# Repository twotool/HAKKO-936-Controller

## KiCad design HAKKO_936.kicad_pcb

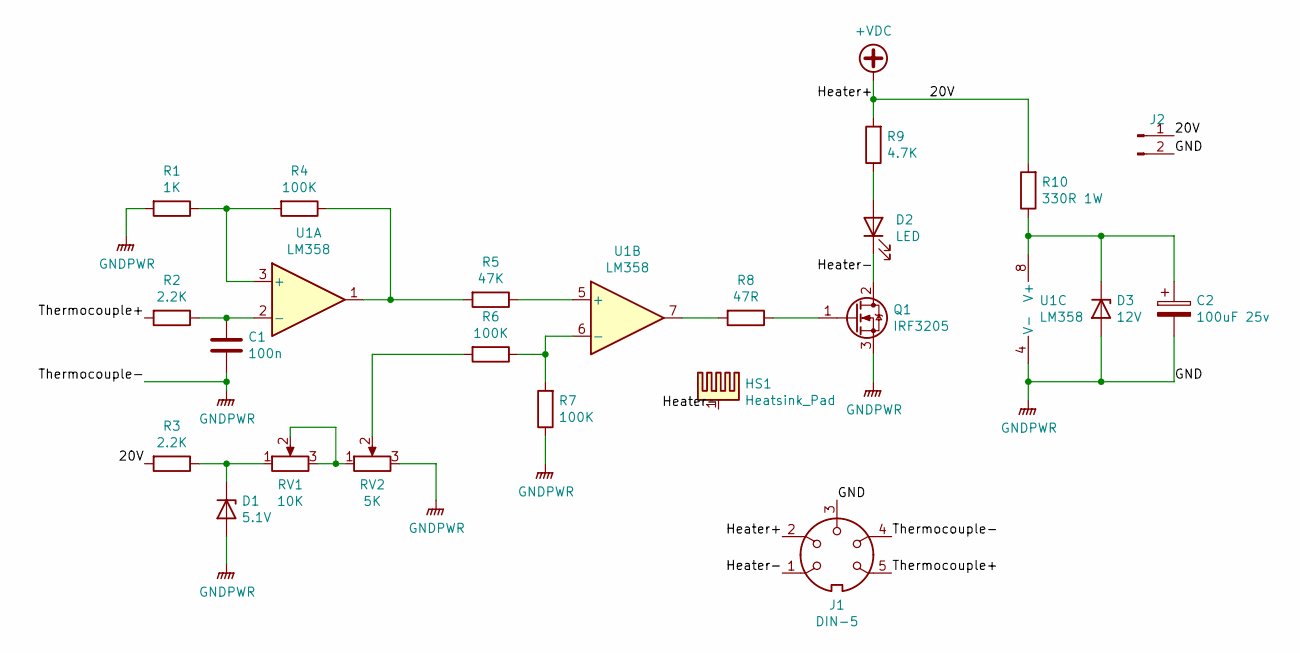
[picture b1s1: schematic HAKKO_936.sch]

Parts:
C1: 100n; C_Disc_D5.0mm_W2.5mm_P2.50mm
C2: 100uF 25v; CP_Radial_D8.0mm_P3.80mm
D1: 5.1V; D_DO-41_SOD81_P10.16mm_Horizontal
D2: LED; LED_D5.0mm
D3: 12V; D_DO-41_SOD81_P10.16mm_Horizontal
HS1: Heatsink_Pad; Heatsink_14x9mm_1xDrill1.5mm
J1: DIN-5; DIN_5_Inline
J2: Conn_01x02_Male; LINE CN
Q1: IRF3205; TO-220-3_Vertical
R1: 1K; R_Axial_DIN0207_L6.3mm_D2.5mm_P10.16mm_Horizontal
R2, R3: 2.2K; R_Axial_DIN0207_L6.3mm_D2.5mm_P10.16mm_Horizontal
R4, R6, R7: 100K; R_Axial_DIN0207_L6.3mm_D2.5mm_P10.16mm_Horizontal
R5: 47K; R_Axial_DIN0207_L6.3mm_D2.5mm_P10.16mm_Horizontal
R8: 47R; R_Axial_DIN0207_L6.3mm_D2.5mm_P10.16mm_Horizontal
R9: 4.7K; R_Axial_DIN0207_L6.3mm_D2.5mm_P10.16mm_Horizontal
R10: 330R 1W; R_Axial_DIN0309_L9.0mm_D3.2mm_P12.70mm_Horizontal
RV1: 10K; Potentiometer_Bourns_3386C_Horizontal
RV2: 5K; Big_POT
U1: LM358; DIP-8_W7.62mm_LongPads

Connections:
+VDC: J1.2, J2.1, R3.2, R9.2, R10.2
/Heater-: D2.1 (K), HS1.1, J1.1, Q1.2 (D)
/Thermocouple+: J1.5, R2.2
GNDPWR: C1.2, C2.2, D1.2 (A), D3.2 (A), J1.3, J1.4, J2.2, Q1.3 (S), R1.2, R7.1, RV2.3, U1.4 (V-)
unnamed: C1.1, R2.1, U1.2 (-)
unnamed: C2.1, D3.1 (K), R10.1, U1.8 (V+)
unnamed: D1.1 (K), R3.1, RV1.1
unnamed: D2.2 (A), R9.1
unnamed: Q1.1 (G), R8.1
unnamed: R1.1, R4.2, U1.3 (+)
unnamed: R4.1, R5.2, U1.1
unnamed: R5.1, U1.5 (+)
unnamed: R6.1, R7.2, U1.6 (-)
unnamed: R6.2, RV2.2
unnamed: R8.2, U1.7
unnamed: RV1.2, RV1.3, RV2.1

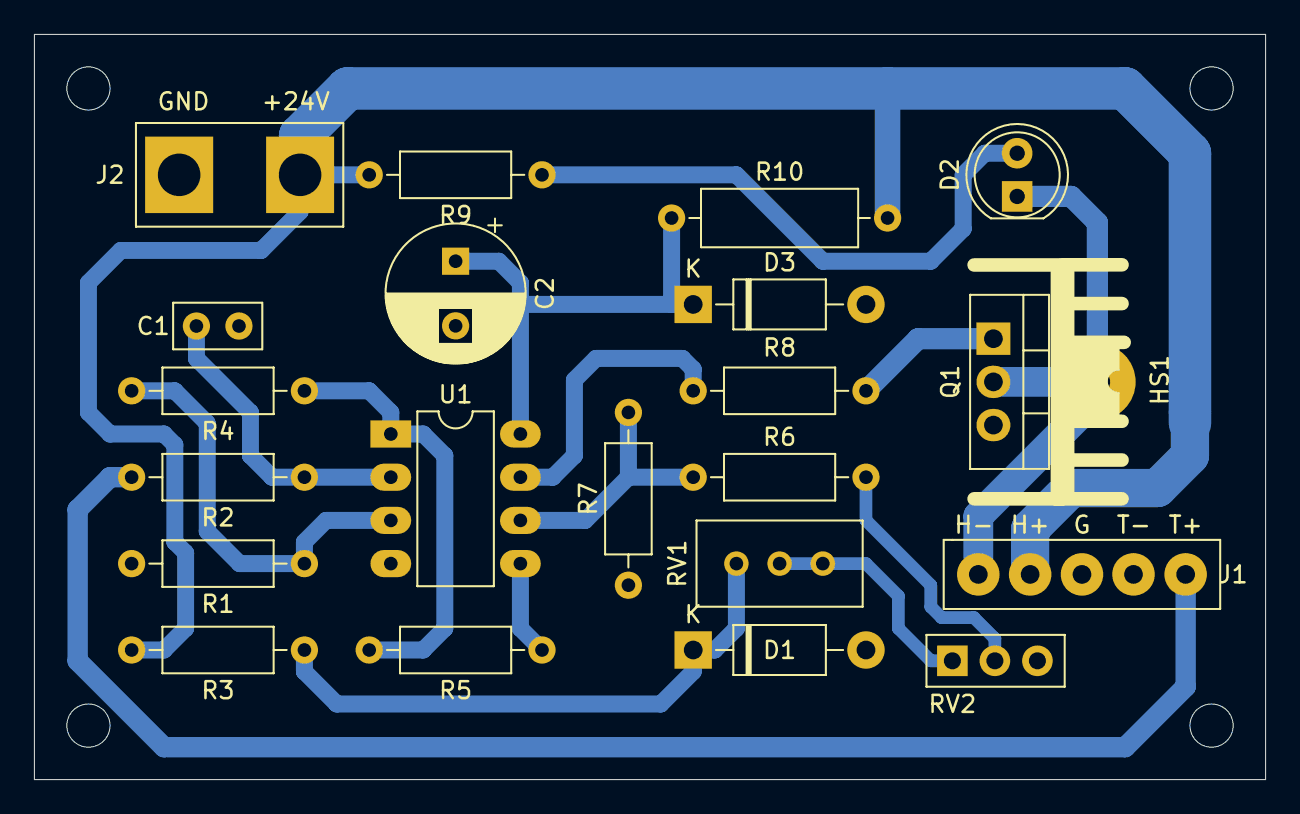
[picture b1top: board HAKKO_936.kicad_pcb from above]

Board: 2 copper layers, 72.4 x 43.8 mm, 22 parts (0 on the bottom side), 16 nets.

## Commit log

2022-07-24 First Commit :)
